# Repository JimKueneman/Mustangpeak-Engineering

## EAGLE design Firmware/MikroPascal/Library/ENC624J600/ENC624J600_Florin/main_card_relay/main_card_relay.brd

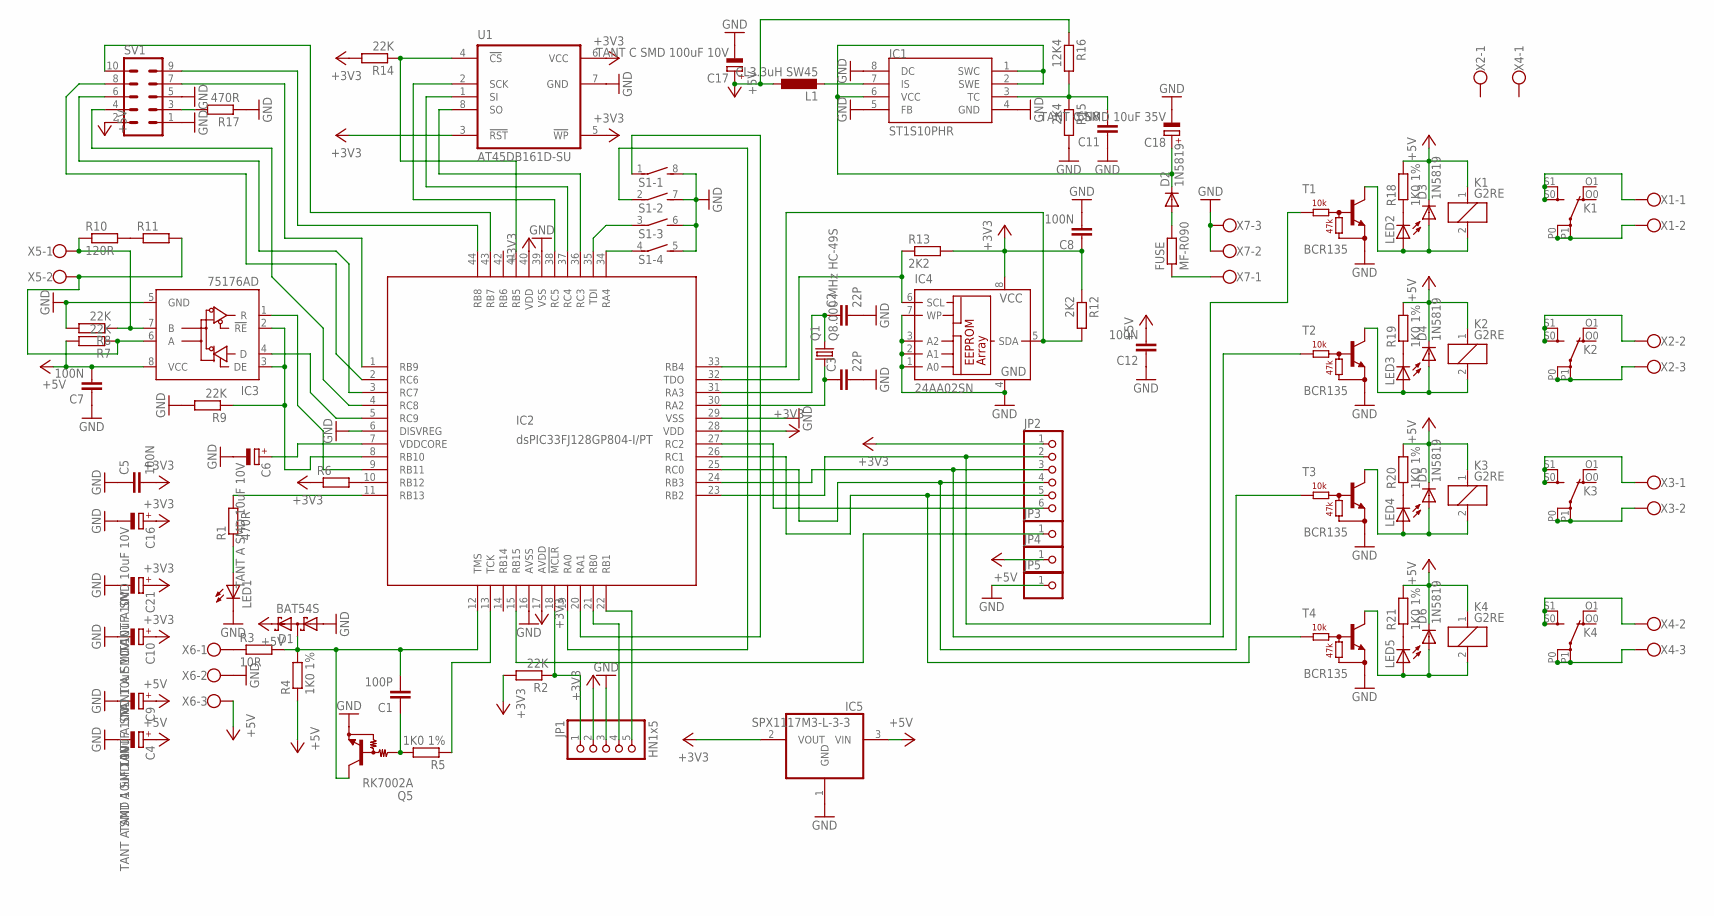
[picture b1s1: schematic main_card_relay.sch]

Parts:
C1: 100P; C0805
C2, C3: 22P; C0805
C4, C6, C9, C10, C16, C21: TANT A SMD 10uF 10V; SMC_A
C5, C7, C8, C12: 100N; C0805
C11: 6N8; C0805
C17: TANT C SMD 100uF 10V; SMC_C
C18: TANT C SMD 10uF 35V; SMC_C
D1: BAT54S; SOT23
D2, D3, D4, D5, D6: 1N5819; DO214AC
FUSE: MF-R090; 0204V
IC1: ST1S10PHR; SOIC8
IC2: dsPIC33FJ128GP804-I/PT; TQFP44
IC3: 75176AD; D_R-PDSO-G8
IC4: 24AA02SN; SO-08
IC5: SPX1117M3-L-3-3; SOT223
JP1: HN1x5; 1X05
JP2: PINHD-1X6; 1X06
JP3, JP4, JP5: PINHD-1X1; 1X01
K1, K2, K3, K4: G2RE
L1: CL3.3uH SW45; 0207/2V
LED1, LED2, LED3, LED4, LED5: LEDCHIPLED_1206; CHIPLED_1206
Q1: Q8.000 MHz HC-49S; HC49/S
Q5: RK7002A; SC59-BEC
R1, R17: 470R; R0805
R2, R7, R8, R9, R14: 22K; R0805
R3: 10R; R0805
R4, R5, R18, R19, R20, R21: 1K0 1%; R0805
R6, R11: R-EU_R0201; R0201
R10: 120R; R0805
R12, R13: 2K2; R0805
R15: 2K4; R0805
R16: 12K4; R0805
S1: DIP04S
SV1: ML10
T1, T2, T3, T4: BCR135; SOT23-R_INFINEON
U1: AT45DB161D-SU; SO08-8S2
X1, X3, X5: W237-102
X2, X4, X6, X7: W237-103

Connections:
+3V3: C5.2, C8.1, C10.+, C16.+, C21.+, IC2.17 (AVDD), IC2.28 (VDD), IC2.40 (VDD), IC4.8 (VCC), IC5.2 (VOUT), JP1.2, JP2.1, R2.2, R6.1, R12.1, R13.2, R14.2, U1.3 (!RST!), U1.5 (!WP!), U1.6 (VCC)
+5V: C4.+, C7.2, C9.+, C12.2, C17.+, D1.2 (C2), D3.C, D4.C, D5.C, D6.C, IC3.8 (VCC), IC5.3 (VIN), JP4.1, K1.1, K2.1, K3.1, K4.1, L1.1, R4.1, R7.2, R16.1, R18.2, R19.2, R20.2, R21.2, SV1.2, X6.3
GND: C2.2, C3.2, C4.-, C5.1, C6.-, C7.1, C8.2, C9.-, C10.-, C11.1, C12.1, C16.-, C17.-, C18.-, C21.-, D1.1 (A1), IC1.4 (GND), IC1.5 (FB), IC1.8 (DC), IC2.6 (DISVREG), IC2.16 (AVSS), IC2.29 (VSS), IC2.39 (VSS), IC3.5 (GND), IC4.1 (A0), IC4.2 (A1), IC4.3 (A2), IC4.4 (GND), IC4.7 (WP), IC5.1 (GND), JP1.3, JP5.1, LED1.C, Q5.E, R8.2, R9.2, R15.2, R17.1, S1.5 (2), S1.6 (2), S1.7 (2), S1.8 (2), SV1.1, SV1.5, T1.2 (E), T2.2 (E), T3.2 (E), T4.2 (E), U1.7 (GND), X6.2, X7.2, X7.3
unnamed: C3.1, IC2.30 (RA2), Q1.1
unnamed: C2.1, IC2.31 (RA3), Q1.2
unnamed: IC2.11 (RB13), R1.2
unnamed: R3.1, X6.1
unnamed: FUSE.1, X7.1
unnamed: IC2.13 (TCK), R5.1
unnamed: IC2.10 (RB12), R6.2
unnamed: IC2.34 (RA4), S1.4 (1)
unnamed: IC2.36 (RC3), U1.8 (SO)
unnamed: IC2.37 (RC4), U1.1 (SI)
unnamed: IC2.38 (RC5), U1.2 (SCK)
unnamed: C6.+, IC2.7 (VDDCORE)
unnamed: IC3.7 (B), R8.1, R10.1, X5.1
unnamed: IC3.6 (A), R7.1, R11.2, X5.2
unnamed: IC2.8 (RB10), IC3.2 (!RE), IC3.3 (DE), R9.1
unnamed: IC2.5 (RC9), IC3.4 (D)
unnamed: IC2.9 (RB11), IC3.1 (R)
unnamed: R10.2, R11.1
unnamed: IC2.33 (RB4), IC4.5 (SDA), R12.2
unnamed: R17.2, SV1.3
unnamed: IC2.35 (TDI), S1.3 (1)
unnamed: IC2.32 (TDO), IC4.6 (SCL), R13.1
unnamed: IC2.44 (RB8), SV1.9
unnamed: IC2.41 (RB5), R14.1, U1.4 (!CS!)
unnamed: IC2.43 (RB7), SV1.10
unnamed: IC2.4 (RC8), SV1.4
unnamed: C1.2, D1.3 (C1A2), IC2.12 (TMS), Q5.C, R3.2, R4.2
unnamed: C1.1, Q5.B, R5.2
unnamed: IC2.18 (!MCLR), JP1.1, R2.1
unnamed: IC2.3 (RC7), SV1.6
unnamed: IC2.2 (RC6), SV1.8
unnamed: IC2.21 (RB0), JP1.4
unnamed: IC2.22 (RB1), JP1.5
unnamed: LED2.C, R18.1
unnamed: IC2.1 (RB9), SV1.7
unnamed: IC2.19 (RA0), S1.2 (1)
unnamed: IC2.20 (RA1), S1.1
unnamed: IC2.24 (RB3), JP2.3, T2.1 (B)
unnamed: D3.A, K1.2, LED2.A, T1.3 (C)
unnamed: K1.P0, K1.P1, X1.2
unnamed: IC2.27 (RC2), JP2.6
unnamed: K1.S0 (S), K1.S1 (S), X1.1
unnamed: IC2.23 (RB2), JP2.2, T1.1 (B)
unnamed: IC2.25 (RC0), JP2.4, T3.1 (B)
unnamed: LED3.C, R19.1
unnamed: D4.A, K2.2, LED3.A, T2.3 (C)
unnamed: IC2.26 (RC1), JP2.5, T4.1 (B)
unnamed: K2.P0, K2.P1, X2.3
unnamed: K2.S0 (S), K2.S1 (S), X2.2
unnamed: LED4.C, R20.1
unnamed: D5.A, K3.2, LED4.A, T3.3 (C)
unnamed: IC2.15 (RB15), JP3.1
unnamed: K3.P0, K3.P1, X3.2
unnamed: D2.A, FUSE.2
unnamed: K3.S0 (S), K3.S1 (S), X3.1
unnamed: LED5.C, R21.1
unnamed: D6.A, K4.2, LED5.A, T4.3 (C)
unnamed: C18.+, D2.C, IC1.1 (SWC), IC1.2 (SWE), IC1.6 (VCC)
unnamed: K4.P0, K4.P1, X4.3
unnamed: K4.S0 (S), K4.S1 (S), X4.2
unnamed: IC1.7 (IS), L1.2
unnamed: C11.2, IC1.3 (TC), R15.1, R16.2
unnamed: LED1.A, R1.1

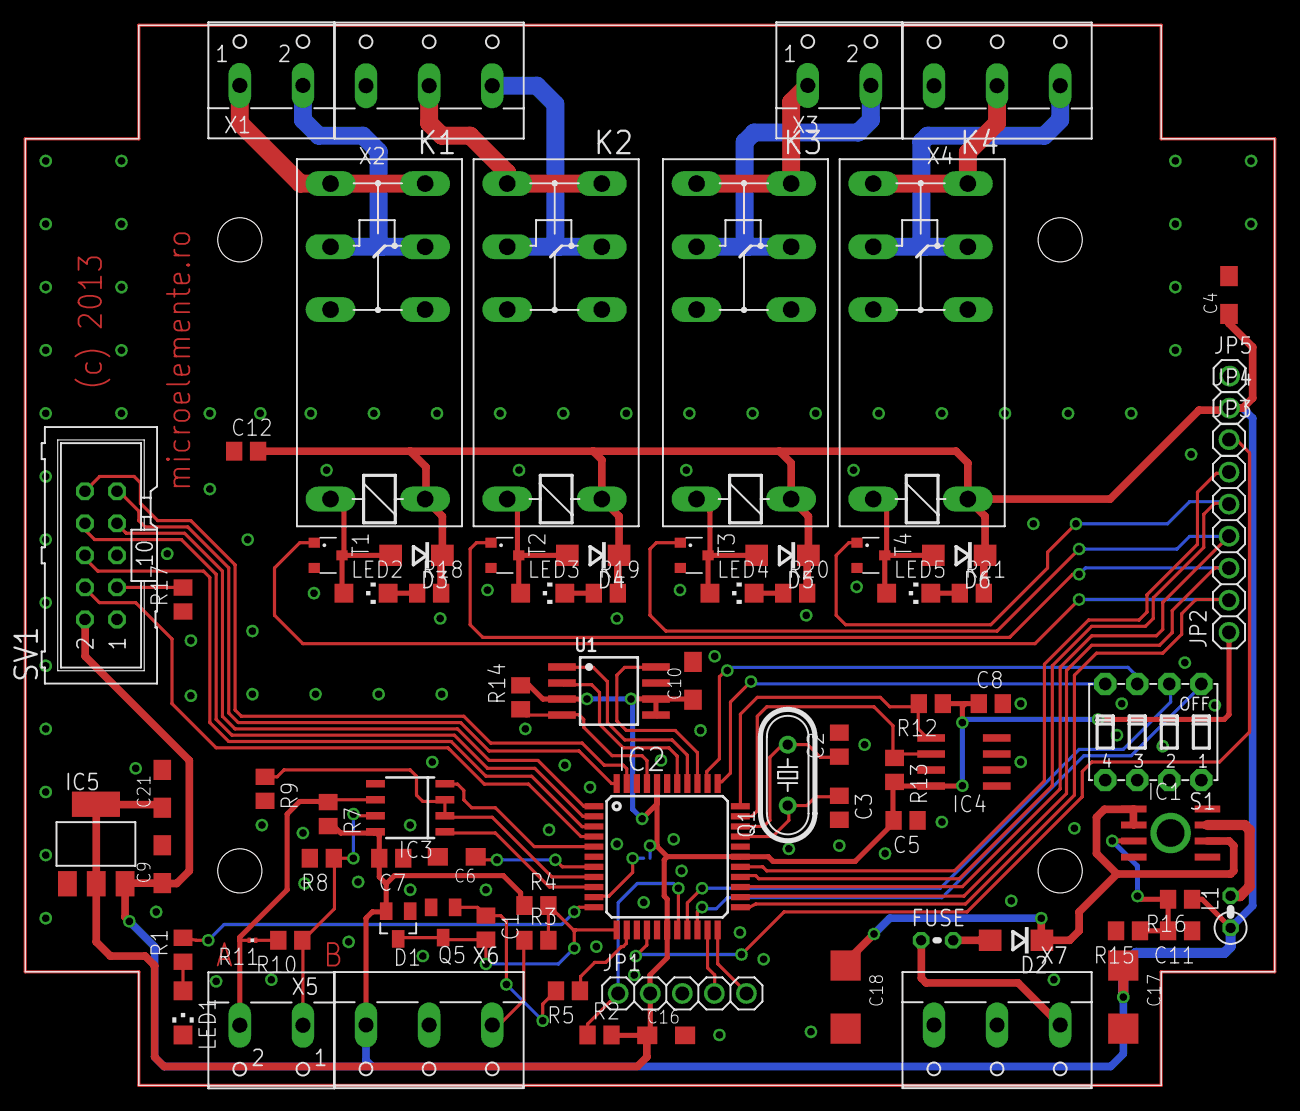
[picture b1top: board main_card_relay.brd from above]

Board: 2 copper layers, 99.0 x 84.0 mm, 80 parts (1 on the bottom side), 66 nets.

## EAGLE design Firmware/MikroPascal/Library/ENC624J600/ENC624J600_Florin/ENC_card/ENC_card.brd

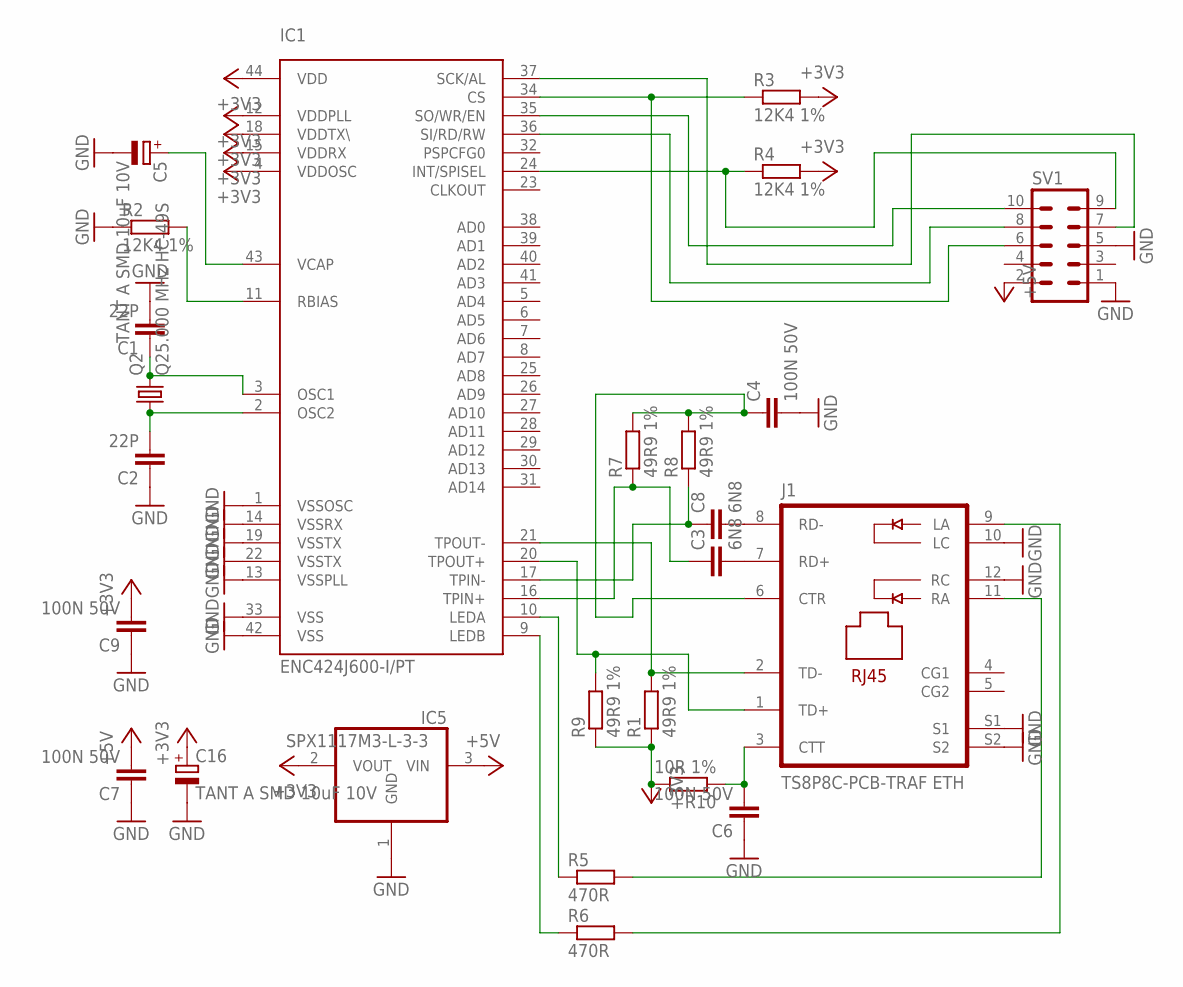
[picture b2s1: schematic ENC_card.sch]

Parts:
C1, C2: 22P; C0805
C3, C8: 6N8; C0805
C4, C6, C7, C9: 100N 50V; C0805
C5, C16: TANT A SMD 10uF 10V; SMC_A
IC1: ENC424J600-I/PT; TQFP44
IC5: SPX1117M3-L-3-3; SOT223
J1: TS8P8C-PCB-TRAF ETH; PJ-J0
Q2: Q25.000 MHz HC-49S; HC49/S
R1, R7, R8, R9: 49R9 1%; R0805
R2, R3, R4: 12K4 1%; R0805
R5, R6: 470R; R0805
R10: 10R 1%; R0805
SV1: ML10L

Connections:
+3V3: C9.2, C16.+, IC1.4 (VDDOSC), IC1.12 (VDDPLL), IC1.15 (VDDRX), IC1.18 (VDDTX\), IC1.44 (VDD), IC5.2 (VOUT), R1.1, R3.2, R4.2, R9.1, R10.2
+5V: C7.2, IC5.3 (VIN), SV1.2
GND: C1.2, C2.1, C4.2, C5.-, C6.1, C7.1, C9.1, C16.-, IC1.1 (VSSOSC), IC1.13 (VSSPLL), IC1.14 (VSSRX), IC1.19 (VSSTX), IC1.22 (VSSTX), IC1.33 (VSS), IC1.42 (VSS), IC5.1 (GND), J1.10 (LC), J1.12 (RC), J1.S1, J1.S2, R2.1, SV1.1, SV1.5
unnamed: IC1.24 (INT/SPISEL), R4.1, SV1.9
unnamed: C8.2, J1.8 (RD-)
unnamed: C2.2, IC1.2 (OSC2), Q2.1
unnamed: C1.1, IC1.3 (OSC1), Q2.2
unnamed: C3.2, J1.7 (RD+)
unnamed: IC1.11 (RBIAS), R2.2
unnamed: C5.+, IC1.43 (VCAP)
unnamed: IC1.34 (CS), R3.1, SV1.6
unnamed: IC1.37 (SCK/AL), SV1.7
unnamed: IC1.36 (SI/RD/RW), SV1.8
unnamed: IC1.35 (SO/WR/EN), SV1.10
unnamed: J1.11 (RA), R5.2
unnamed: J1.9 (LA), R6.2
unnamed: C6.2, J1.3 (CTT), R10.1
unnamed: IC1.21 (TPOUT-), J1.2 (TD-), R1.2
unnamed: IC1.20 (TPOUT+), J1.1 (TD+), R9.2
unnamed: C4.1, J1.6 (CTR), R7.2, R8.2
unnamed: C8.1, IC1.17 (TPIN-), R8.1
unnamed: C3.1, IC1.16 (TPIN+), R7.1
unnamed: IC1.10 (LEDA), R5.1
unnamed: IC1.9 (LEDB), R6.1

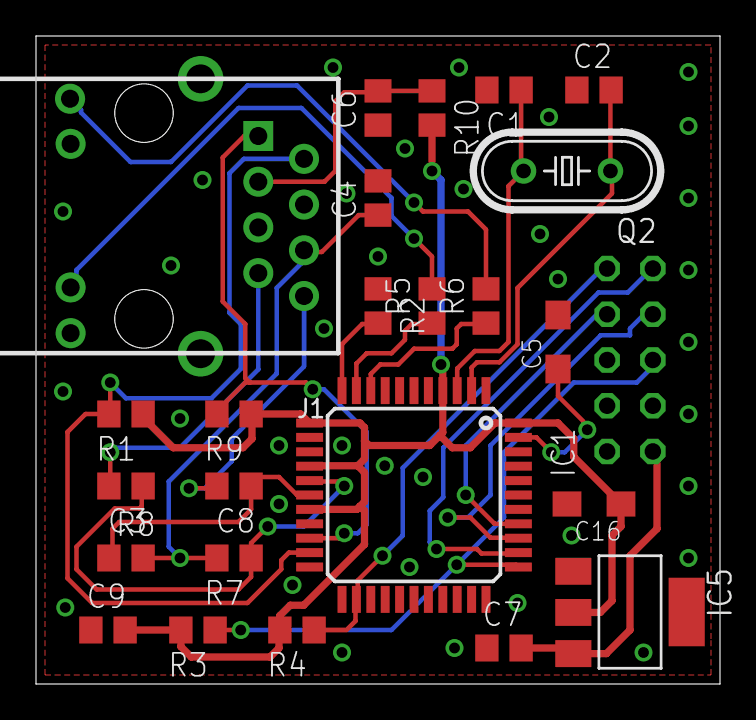
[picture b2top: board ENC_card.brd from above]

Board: 2 copper layers, 38.0 x 36.0 mm, 25 parts (1 on the bottom side), 24 nets.

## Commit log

2015-09-01 Initial Checkin
2015-09-01 - Added Raspberry Pi CAN Adapter Hardware Files
2015-09-01 Moved the Bootloader code to Mustangpeak Engineering Repository
2015-09-22 Changed way CAN Rx worked. Manager buffer myself.
2015-10-18 - Debug build of the CAN/Ethernet Adapter
2015-10-19 - More special builds of the CAN/Ethernet adapter to run down performance and bugs
2015-10-20 - Working towards a working Ethernet/CAN hub
2015-10-20 - Ready to test on the Ethernet to CAN adapter breadboard!
2015-10-21 - Syncing
2015-10-25 - Debugging the RPi, drops a message once in a while
2015-10-26 - RPi working on the dsPIC33EP512GP810 - Started update on the Layout
2015-10-28 - Updates on the RPi - CAN PWB - Added Datasheets for circuit - Compiled Hub with the dsPIC33EP64GP502
2015-10-31 - Layout ready?
2015-11-02 - Layout Builder in FireMonkey started.
2015-11-02 - Learning about Touch messages with mobile devices...
2015-11-03 - RPiCAN Adapter layout complete - Created a 3x3 panel of RPiCAN board for fab. - One more check and order will go out.
2015-11-03 - Fixed bad pad
2015-11-04 - Archive RPiCAN version -Dash
2015-11-08 - RPi CAN/Ethernet hub working!
2015-11-08 - Fixed bug but will likely break everything….
2015-11-08 - Long hard battle with the dsPIC SPI module but I now understand its nuances. Ethernet to CAN working. Ready for my custom PWBs
2015-11-12 - Functional CAN/Ethernet dsPIC code on the dsPIC33EP256GP502 on the custom RPiCAN board!
2015-11-12 - Started on Rev A layout fixing the regulator problem
2015-11-12 Fixed DRC errors in Rev A of the RPiCAN board
2015-11-15 - RPi Ethernet to CAN bridge working. Started on the Bootloader over SPI
2015-11-15 - Work on the RPiCAN hub dsPIC
2015-11-15 - Flash reprogramming and org in dsPIC33 RPiCAN coded…. needs testing
2015-11-16 - More work on the dsPIC code
2015-11-17 - Fixed bug in boot loader address calculations
2015-11-20 Xon/Xoff from the RPi to the dsPIC functional and tested.
2015-11-20 - Fixed bug with RPiCAN code
2015-11-25 - Functional Bootloader on the Pi over SPI
2015-11-26 - Started evaluating a DCC Booster on the Pi
2016-01-11 - Work on CCA for Tortious Pi
2016-02-06 - Small updates
2016-09-09 - CAN to Ethernet bridge working under Ultibo!
2017-01-21 New fork to better work with Ultibo and getting rid of the CAN stuff..
2017-01-22 Removed a few threads and updated to compile with all protocols
2017-01-22 - Bit of renaming of units for consistency - Decided not supporting CAN internally adds too much complexity, from this point on will re-enabled CAN support internally.
2017-01-31 Working
2017-01-31 Merging
2017-02-02 Complies in Ultibo need to fill out wrappers that look like Synapse
2017-04-17 Work towards converter away from Synapse on Ultibo
2017-04-17 Added Generics
2017-04-18 More testing with Ultibo and the Listen class
2017-04-19 Fixed to compile in other than Ultibo
2017-04-19 Ultibo compiling with Synapse!
2017-04-19 Garry had synautil.pas already fixed and I did not copy the changes.
2017-04-19 Merged the branch of converting back to Synapse
2017-04-19 Synapse modified to compile with Ultibo!!!!! Need to test!!!
2017-04-23 Fixed more issues with Ultibo. Still need the StopTimer issue fixed.
2017-04-23 Changed the Timer implantation so I don’t StopTimer since it hangs on Ultibo
2017-04-23 Forgot changes for the Timer
2017-04-30 No much to talk about. Minor things.
2017-05-03 - Created a VirtualTreeview Package and worked on the implementation. DragSelect Rect working
2017-05-03 - Cleanup
2017-05-20 - Updated to compile and work with Delphi
2017-05-29 - Lcc Library, Synapse and Mustangpeak library working with Delphi mobile as well as Ultibo. Also started working on a LccThrottle project in Delphi Seattle.
2017-06-12 - Mostly working with TSelection but it is becoming clear working around that selection class is not worth the aggravation. Looking at doing it manually.
2017-06-15 Started Branch with new ideas for selection. Working great so far.
2017-06-15 Selection working great.
2017-06-18 Selection Merged
2017-06-18 Fixed some missing links
2017-06-19 Deployed on iPad, iPhone, iPod and Android with a few bugs fixed.
2017-06-20 - Updated to rotate correctly between landscape and portrait modes when the device is rotated. For iOS it MUST be built against the iOS8 SDK to work on iOS7 and iOS9
2017-06-20 - Realigned Drag functions to the new Sketchpad
2017-06-22 Some work on Tap and mobile drag-drop
2017-07-14 Drag Select and Dragging mostly working.... FINALLY
2017-07-14 Started implementing Streaming the layout items.
2017-07-15 XML Save and Load functional!
2017-07-17 Refactored to have a SelectableObject base classes and make selection automatic
2017-07-19 Reworking the Select Logic Refactored much of the drag logic into the TDragManager unit.
2017-07-29 - Copy/Paste through XML complete
2017-11-15 Automotive Firmware and Designs
2017-11-15 Syncing
2017-11-15 Added Design Files and App Notes to the Automotive Area
2017-11-15 Added Datasheet
2017-11-15 Electronic Ignition Working with 32bit CCP Timers
2017-11-16 Updated Spreadsheet to include total energy for IGBT selection
2017-11-17 Code tested with a real coil!
2017-11-22 More work on the Mopar Electronic Ignition. Code needs a derivative; the circuit is placed and fits.
2017-11-22 Copied the PCB Architect libraries to this archive for future use. Need to abandon the one in OLCB now.
2017-11-22 Converted PCB Architect to Libraries in this archive
2017-11-22 Reorganized the PCB Architect folder
2017-11-23 Converted the Compare Timers to actual Timers in the PIC24FV32KA301 device. Ready for test.
2017-11-23 Optimized the code for variable dwell.
2017-11-24 Started working on the advance curve code
2017-11-24 Added datasheets
2017-11-24 - Updated Design Spreadsheet
2017-11-24 More work on Advance Map
2017-11-25 Advance Map functional and mostly tested. Needs more rigiours testing.
2017-11-28 Double Pulse Code Added
2017-11-28 - Fixed DWORD to REAL conversion problem
2017-11-28 - ADC Datasheet added
2017-11-28 Calculated Blanking a bit different
2017-12-03 Layout complete. Needs full checkout.
2017-12-03 More files from layout
2017-12-03 Double Pulse Filter Code function and tested
2017-12-03 Added Simple Filter and Digital Filter Layout to the PWB
2017-12-03 Cleaned up Ignitor Layout
2017-12-09 double pulse on the 101 part functional
2017-12-09 Stored the POD version of the ignition board
2017-12-10 Updated the 101 Double Pulse to try to handle startup better.
2017-12-10 New checks and added state machine
2017-12-10 - Successful Drive that worked flawlessly!
2017-12-11 - Added Datasheet for connectors
2017-12-11 - Working to update PWB with testing results
2017-12-12 - Started working on adding connectors and updating based on the testing
2017-12-12 - Updated components with part numbers and correct values
2017-12-14 - Major update in the 101 Double Pulse code. Implemented the waiting for a clean valid RPM after starting cranking and a way to send the FiTech the fake RPM to shoot fuel sooner.
2017-12-15 - Updated the 304 Double Pulse Code - Split out the double pulse filter PWB layout from the ignitor
2017-12-15 - Updated the Passive Filter PWB - Update the new standalone Ignitor PWB
2017-12-17 - Updated 101 Double Pulse Code
2017-12-17 - Added some data sheets - Updated the layout - Debugged the 101 Code on the bench. Found several bugs.... Will it work now? Maybe.
2017-12-17 - fixed bug with the Fake RPM to prime the FiTech
2017-12-18 - More work on the Double Pulse PWB
2017-12-18 - Couple more tweaks to the 101 Double Pulse Code
2017-12-19 - Digital Filter PWB ready for ground pour
2017-12-20 - More work on the POD2 PWB
2017-12-22 More work on the 301 code and layout
2017-12-22 - Update on the 101
2017-12-22 301 code functioning on the car
2017-12-24 - Basic Ignitor code working and IO pins mapped and functional on the PWB.
2017-12-24 - Double Pulse working on the Car. Drove it to Oro Valley and back. On the way on freeway a few surges and double RPM events.
2017-12-26 Updates to the 301 code to add debugging in the car
2017-12-26 Work on the Ignitor Code
2017-12-26 Added commands through the UART to control debut outputs
2018-01-02 Added a debug mode that is untested. Have a better idea. Gonna do a branch
2018-01-02 - Functionally working. Test drive shows a few things I don't understand
2018-01-03 - Branch working really good (Fixed_RPM_FiTech)
2018-01-03 Added note for components used with Pertronix ignitor on the Dual Pulse Filter
2018-01-03 - Fixed initialization of the Filter bug and cleaned up code
2018-01-03 - Fixed bug in the RPM Logging
2018-01-05 - Reduced the filtering on the double pulse filter to 3 - Work-on the layout....
2018-01-16 - Started FiTech VE Helper Tools
2018-01-20 FiTech Tools update
2019-06-16 Added EveWiFi Project
2019-06-26 Updates on VirtualListview for Lazarus
2019-06-26 Saving EngineAnalyzer program
2019-06-30 Many updates and improvements
2019-06-30 Lots more updates and features added, selection, focus, collapsing
2019-07-01 More updates and improvements
2019-07-06 More updates and features in VirtualListview
2019-07-07 Ctrl-Click Select implemented..... finally.....
2022-06-02 Retirement App
2023-08-21 Started my Javascript Journey
2023-08-21 Javascript files
2023-08-21 UI updates
2023-08-22 reworking the database access to make it real, markers still need to be created.
2023-08-23 database working
2023-08-25 refactored and text pasting started to be implemented.
2024-12-19 Lots of updates
2025-05-21 Simulation Models for TurnoutBoss

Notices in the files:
Firmware/MikroPascal/Library/ENC624J600/ENC624J600_Florin/main_card_relay/main_card_relay.brd:
(c) 2013
